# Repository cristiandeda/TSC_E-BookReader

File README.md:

# TSC_E-BookReader

## Diagrama bloc:

## Pasi de implementare:

- Am creat **schema electrica** pe baza celei atasate in cerinta, folosind biblioteca `DeskAssistant`
- Am creat apoi **PCB**-ul:
    - am modificat dimensiunile PCB-ului pentru a corespunde cu cele descrise in cerinta
    -  am plasat componentele in functie de schema electrica, grupandu-le pe baza 'functionalitatii'
    -  am decupat PCB-ul conform fisierului atasat in enunt
    -  am modificat denumirile *test-pad-urilor* - *TP* in functie de semnalele pe care le poarta
    -  am facut autorutare cu dimensiunile traseelor de alimentare precizate in enunt (`VBUS`, `VUSB`, `VBAT`, `3V3`, `EPD_3V3` si `EPD_3V3_C` cu *CopperWidth* de minimum **0.3 mm**, iar restul cu *CopperWidth* de minimum **0.15 mm**)
    -  am trasat planurile de masa (*top* si *bottom*)
- Am introdus modelele **3D**:
    - am descarcat modelele 3D corespunzatoare de pe [Component Search Engine](https://componentsearchengine.com/)
    - am editat fiecare componenta, adaugandu-i modelul 3D pe care l-am pozitionat conform *pinilor* / *footprint-ului*
- Am desenat modelele **3D** pentru *baterie*, *ecran* si *test-pad-uri* tinand cont de dimensiuni
- Am adaugat toate piesele (*placuta*, *ecranul*, *bateria* si *carcasa*) obtinand produsul final

## Descriere functionalitate hardware:

### 1. Alimentare și Protecție (USB-C & ESD)
- **Conector USB-C**: permite alimentarea plăcii și comunicarea de date.
- **PFMF.050.1**, **TVS diode (D1)**: oferă protecție la supratensiuni și descărcări electrostatice.
- **IC1**: convertește tensiunea de intrare (5V) la 3.3V, necesară pentru alimentarea circuitelor logice (ESP32, senzori, etc.).

### 2. Control Alimentare Baterie
- **MCP73831** este un controler de încărcare pentru baterii Li-Po.
- **C1, C2** filtrează zgomotele pe linia de alimentare.
- Permite alimentarea sistemului din baterie reîncărcabilă și oferă protecție la supraîncărcare/descărcare.

### 3. Nivel Încărcare Baterie
- **MAX17048** măsoară nivelul de încărcare al bateriei.
- Comunicarea se face prin magistrala I2C (SCL/SDA), comună cu alți senzori.
- Permite afișarea nivelului bateriei pe ecran sau transmiterea sa prin rețea.

### 4. Afișaj E-Paper
- **Header E-Paper** conectează un afișaj de tip E-Ink.
- **Driverul de semnal (MBR0530, L1, Q3)** controlează alimentarea și semnalele de comutare pentru afișaj.
- Selectarea tipului de ecran se face cu jumperul **S1**.
- Afișajul e-paper este ideal pentru consum redus de energie.

### 5. Modul RTC (Ceas în timp real)
- **DS3231SN** menține ora exactă, chiar și când placa este oprită.
- Funcționează pe I2C și are o baterie de rezervă.

### 6. Senzor Ambiental (BME688)
- Măsoară temperatură, umiditate, presiune și calitatea aerului.
- Se conectează la ESP32 prin I2C.

### 7. Memorie NOR Flash externă (64MB)
- **W25Q512JVEIQ** este o memorie SPI folosită pentru stocare extinsă (ex: cărți, imagini, date).
- Conectată la ESP32 pe interfață SPI (IO4–IO7).
- Permite stocarea persistentă a fișierelor.

### 8. Cititor Card SD
- Slot SD conectat prin SPI (IO8–IO11).
- Permite acces la fișiere externe, jurnalizare sau încărcare de date din card.

### 9. ESP32-C6 - Microcontroller Principal
- Conectează toate perifericele și controlează logica sistemului.
- Suportă Wi-Fi 6, BLE 5.2 și Zigbee/Thread.
- Are GPIO configurate pentru SPI, I2C, UART și control E-Paper.
- Este nucleul care rulează software-ul aplicației.

### 10. Protecții ESD pe SPI & Qwiic
- Diodă **TVS** și rezistențe pe liniile SPI/Qwiic pentru protecție la ESD.
- Asigură durabilitate mai mare în aplicații reale.

### 11. Butoane - Reset & Boot
- Buton **RESET**: Repornește ESP32.
- Buton **BOOT**: Permite intrarea în mod de boot pentru programare.
- Ambele conectate la pini critici (EN, IO0).

### 12. Interfață Qwiic / Stemma QT
- Conector I2C standard (JST-SH 4 pini).
- Permite adăugarea rapidă de senzori sau module adiționale compatibile.

### 13. Test Pads
- Paduri expuse pentru GPIO-uri esențiale.
- Permit depanarea, măsurători și extinderea funcționalității.

---

## Descrierea pinilor ESP32-C6:

| Pin ESP32-C6 | Nume Semnal     | Componentă Asociată                   | Scop / Funcție                                           |
|--------------|------------------|----------------------------------------|-----------------------------------------------------------|
| GND          | GND              | Toate componentele                     | Masă comună pentru alimentare și semnal.                  |
| EN           | Enable           | Buton Reset                            | Resetează microcontrollerul la apăsare.                   |
| IO0          | GPIO0            | Buton BOOT                             | Intrare în modul de boot la apăsare.                      |
| IO1          | GPIO1            | Test Pad TP11                          | Test/debug sau I/O general.                               |
| IO2          | GPIO2            | Test Pad TP12                          | Test/debug sau I/O general.                               |
| IO3          | GPIO3            | Test Pad TP13                          | Test/debug sau I/O general.                               |
| IO4          | GPIO4            | SPI Flash (CS)                         | Chip Select pentru memoria NOR Flash externă.             |
| IO5          | GPIO5            | SPI Flash (CLK)                        | Clock SPI pentru memoria NOR Flash externă.               |
| IO6          | GPIO6            | SPI Flash (MISO)                       | Data Out din NOR Flash spre ESP32.                        |
| IO7          | GPIO7            | SPI Flash (MOSI)                       | Data In către NOR Flash de la ESP32.                      |
| IO8          | GPIO8            | SD Card (CS)                           | Chip Select pentru card SD.                               |
| IO9          | GPIO9            | SD Card (CLK)                          | Clock SPI pentru card SD.                                 |
| IO10         | GPIO10           | SD Card (MISO)                         | Date de pe card SD către ESP32.                           |
| IO11         | GPIO11           | SD Card (MOSI)                         | Date de la ESP32 către card SD.                           |
| IO12         | GPIO12           | E-Paper Header                         | Semnal pentru ecran E-Paper (ex: BUSY, RST etc.).         |
| IO13         | GPIO13           | E-Paper Header                         | Semnal pentru ecran E-Paper.                              |
| IO14         | GPIO14           | E-Paper Header                         | Semnal pentru ecran E-Paper.                              |
| IO15         | GPIO15           | E-Paper Header                         | Semnal pentru ecran E-Paper.                              |
| IO16         | GPIO16           | SCL (RTC & BME688)                     | I2C Clock comun pentru RTC și senzor de mediu.            |
| IO17         | GPIO17           | SDA (RTC & BME688)                     | I2C Data comun pentru RTC și senzor de mediu.             |
| IO18         | GPIO18           | UART_RX (Qwiic/Debug)                  | Recepție serială (debug sau Qwiic/StemMA).                |
| IO19         | GPIO19           | UART_TX (Qwiic/Debug)                  | Transmisie serială (debug sau Qwiic/StemMA).              |

## Bill of Materials (BOM):

| Componenta |        Link      |               Datasheet                |
|------------|------------------|----------------------------------------|
| ESP32-C6-WROOM-1-N8 | [Link](https://ro.mouser.com/ProductDetail/Espressif-Systems/ESP32-C6-WROOM-1-N8?qs=8Wlm6%252BaMh8ST02Gmwp74cw%3D%3D) | [Datasheet](https://ro.mouser.com/datasheet/2/891/Espressif_ESP32_C6_WROOM_1__Datasheet_V0_1_PRELIMI-3239987.pdf) |
| 112A-TAAR-R03_ATTEND | [Link](https://www.digikey.ro/ro/products/detail/attend-technology/112A-TAAR-R03/17633923) | [Datasheet](https://www.attend.com.tw/data/download/file/112A-TAAR-R03_Spec.pdf) |
| ADAFRUIT_LEDCHIP-LED0603 | [Link](https://www.snapeda.com/parts/KP-1608SURCK/Kingbright/view-part/?ref=search&t=LED%200603) | [Datasheet](https://www.snapeda.com/parts/KP-1608SURCK/Kingbright/datasheet/) |
| ESP32_WROVER_EAGLE-LTSPICE_RR0402 | [Link](https://www.snapeda.com/parts/RC0402FR-07226RL/Yageo/view-part/) | [Datasheet](https://www.snapeda.com/parts/RC0402FR-07226RL/Yageo/datasheet/) |
| ESP32_WROVER_EAGLE-LTSPICE_CC0402 | [Link](https://componentsearchengine.com/part-view/CC0402MRX5R5BB106/YAGEO) | [Datasheet](https://componentsearchengine.com/Datasheets/2/CC0402MRX5R5BB106.pdf) |
| RCL_CPOL-EUCT3528 | [Link](https://ro.mouser.com/ProductDetail/Vishay-Sprague/TR3B106K025C1300?qs=jCGqFXxTmLdffnuDkXzk1g%3D%3D) | [Datasheet](https://www.vishay.com/docs/40080/tr3.pdf) |
| ESP32_WROVER_SPARKFUN-DISCRETESEMI_MOSFET_PCH-DMG2305UX-7 | [Link](https://ro.mouser.com/ProductDetail/Diodes-Incorporated/DMG2305UX-7?qs=L1DZKBg7t5F%2FNBHrjfxC%252Bg%3D%3D) | [Datasheet](https://www.diodes.com/assets/Datasheets/DMG2305UX.pdf) |
| 744043680IND_4828-WE-TPC_WRE | [Link](https://www.digikey.sg/en/products/detail/w%C3%BCrth-elektronik/744043680/1638515) | [Datasheet](https://www.we-online.com/components/products/datasheet/744043680.pdf) |
| BD5229G-TR | [Link](https://ro.mouser.com/ProductDetail/ROHM-Semiconductor/BD5229G-TR?qs=4kLU8WoGk0vvnhrrYwdszw%3D%3D) | [Datasheet](https://fscdn.rohm.com/en/products/databook/datasheet/ic/power/voltage_detector/bd52xxg-e.pdf) |
| ESP32_WROVER_BME680_BME680 | [Link](https://ro.mouser.com/ProductDetail/Bosch-Sensortec/BME680?qs=v271MhAjFHjo0yA%2FC4OnDQ%3D%3D) | [Datasheet](https://ro.mouser.com/datasheet/2/783/BST_BME680_DS001-1509608.pdf) |
| BUTTON_CUSYOMV1 | [Link](https://ro.mouser.com/ProductDetail/Panasonic/EVQ-P7M01P?qs=rJ%252BziJWpysz0sJAzuCybtw%3D%3D) | [Datasheet](https://industry.panasonic.com/global/en/downloads/?file_cd=402906&tab=catalog&series_cd=3457) |
| CPH3225A | [Link](https://ro.mouser.com/ProductDetail/Seiko-Semiconductors/CPH3225A?qs=3etwrb1wR%252BhUOph6lAO7eg%3D%3D) | [Datasheet](https://ro.mouser.com/datasheet/2/360/Seiko_Instruments_MicroBattery_E_20230330_2024Jan_-3561061.pdf) |
| DS3231SN# | [Link](https://ro.mouser.com/ProductDetail/Analog-Devices-Maxim-Integrated/DS3231SN?qs=1eQvB6Dk1vhUlr8%2FOrV0Fw%3D%3D) | [Datasheet](https://ro.mouser.com/datasheet/2/609/DS3231-3421123.pdf) |
| ESP32C6_VARISTORCN1812 | [Link](https://eu.mouser.com/ProductDetail/KEMET/VC1812L501R008?qs=jj7GbYRQuOa1j1%2F3gPpdvQ%3D%3D) | [Datasheet](https://eu.mouser.com/datasheet/2/447/KEM_V0002_VC-3316862.pdf) |
| ESP32_WROVER_AVX---SD0805S020S1R0_AVX_SD0805S020S1R0_0_0AVX_SD0805S020S1R0_0_0 | [Link](https://eu.mouser.com/ProductDetail/KYOCERA-AVX/SD0805S020S1R0?qs=jCA%252BPfw4LHbpkAoSnwrdjw%3D%3D&utm_id=6470900573&utm_source=google&utm_medium=cpc&utm_marketing_tactic=emeacorp&gad_source=1&gbraid=0AAAAADn_wf2CZaBvMXoqDoLB8a6wI1EC_&gclid=CjwKCAjw--K_BhB5EiwAuwYoyhyp4YPMQJxEs9O7Um1pbb_qrwD9UbwWFHYqYH_KvU5-nXs4CTfFVRoCY7kQAvD_BwE) | [Datasheet](https://eu.mouser.com/datasheet/2/40/schottky-3165252.pdf) |
| FH34SRJ-24S-0.5SH_99_ | [Link](https://eu.mouser.com/ProductDetail/Hirose-Connector/FH34SRJ-24S-05SH99?qs=vcbW%252B4%252BSTIpKBl5ap9J8Fw%3D%3D&utm_id=6470900573&utm_source=google&utm_medium=cpc&utm_marketing_tactic=emeacorp&gad_source=1&gbraid=0AAAAADn_wf2CZaBvMXoqDoLB8a6wI1EC_&gclid=CjwKCAjw--K_BhB5EiwAuwYoykKExbMK_Nf7-m2eYAFcWwWt_BaAKmDd5HmJ3DzOwus-MUIZVeL9ExoCTtAQAvD_BwE) | [Datasheet](https://eu.mouser.com/datasheet/2/185/FH34SRJ_24S_0_5SH_99__CL0580_1255_6_99_2DDrawing_0-1615044.pdf) |
| MAX17048G+T10 | [Link](https://eu.mouser.com/ProductDetail/Analog-Devices-Maxim-Integrated/MAX17048G+T10?qs=D7PJwyCwLAoGnnn8jEPRBQ%3D%3D&utm_id=20109199409&utm_source=google&utm_medium=cpc&utm_marketing_tactic=emeacorp&gad_source=1&gbraid=0AAAAADn_wf23I7VSL8Khkvz-kjEhjYqPz&gclid=CjwKCAjw--K_BhB5EiwAuwYoytVFz576awyE1ug3GUFRWVeGavv1g_gzDMEDxxjVwp1JIOS60JmKnhoC-zIQAvD_BwE) | [Datasheet](https://eu.mouser.com/datasheet/2/609/MAX17048_MAX17049-3469099.pdf) |
| MBR0530 | [Link](https://eu.mouser.com/ProductDetail/Micro-Commercial-Components-MCC/MBR0530-TP?qs=KFo7JewZbUECRHkxGanrdg%3D%3D&utm_id=6470900573&utm_source=google&utm_medium=cpc&utm_marketing_tactic=emeacorp&gad_source=1&gbraid=0AAAAADn_wf2CZaBvMXoqDoLB8a6wI1EC_&gclid=CjwKCAjw--K_BhB5EiwAuwYoysNC_AmHFOx6dFFFiTr86y8jRKC674aUhl0na6xIgHM9UWT_XyhG0RoCYwIQAvD_BwE) | [Datasheet](https://eu.mouser.com/datasheet/2/258/MBR0520_MBR0580_SOD123_-2492194.pdf) |
| ESP32_WROVER_SPARKFUN-IC-POWER_MCP73831 | [Link](https://ro.mouser.com/ProductDetail/Microchip-Technology/MCP73831-2DCI-MC?qs=hH%252BOa0VZEiBQ%2FrptDRXKdg%3D%3D) | [Datasheet](https://ro.mouser.com/datasheet/2/268/MCP73831_Family_Data_Sheet_DS20001984H-3441711.pdf) |
| PGB1010603MR | [Link](https://ro.mouser.com/ProductDetail/Littelfuse/PGB1010603MR?qs=gu7KAQ731URLg4GSnNNN7Q%3D%3D) | [Datasheet](https://www.littelfuse.com/assetdocs/pulseguard-esd-suppressors-pgb1-datasheet?assetguid=8a337998-d54d-466b-be4e-dc5bcd1f9321) |
| QWIIC_CONNECTORJS-1MM | [Link](https://www.sparkfun.com/qwiic-jst-connector-smd-4-pin-vertical.html) | [Datasheet](https://www.jst-mfg.com/product/pdf/eng/eSH.pdf?5ec58813d214e) |
| SAMACSYS_PARTS_USB4110-GF-A | [Link](https://eu.mouser.com/ProductDetail/GCT/USB4110-GF-A?qs=KUoIvG%2F9IlYiZvIXQjyJeA%3D%3D&utm_id=6470900573&utm_source=google&utm_medium=cpc&utm_marketing_tactic=emeacorp&gad_source=1&gbraid=0AAAAADn_wf2CZaBvMXoqDoLB8a6wI1EC_&gclid=CjwKCAjw--K_BhB5EiwAuwYoyqoFYku-1KEnaVMBZNhraqam0ThMUfxlrF7A4GQ8Pqj9d6zLqr7juBoCrOEQAvD_BwE) | [Datasheet](https://eu.mouser.com/datasheet/2/837/GCT_USB4110_Product_Drawing___20k_cycles-3455479.pdf) |
| SI1308EDL-T1-GE3 | [Link](https://eu.mouser.com/ProductDetail/Vishay-Semiconductors/SI1308EDL-T1-GE3?qs=bX1%252BNvsK%2FBramh9tgpOaEw%3D%3D&utm_id=20109199409&utm_source=google&utm_medium=cpc&utm_marketing_tactic=emeacorp&gad_source=1&gbraid=0AAAAADn_wf23I7VSL8Khkvz-kjEhjYqPz&gclid=CjwKCAjw--K_BhB5EiwAuwYoyllRgbebqlW1QDUb9SQpEls061aMn76tZxer07jsniKXNOsDESHnSBoCkL8QAvD_BwE) | [Datasheet](https://www.vishay.com/docs/63399/si1308edl.pdf) |
| USBLC6-2SC6Y | [Link](https://eu.mouser.com/ProductDetail/STMicroelectronics/USBLC6-2SC6Y?qs=gNDSiZmRJS%2FOgDexvXkdow%3D%3D&srsltid=AfmBOoqlX0fgvKlHMd5oyRC9Sr6hBsf51Zi0RKmaIGejNRz6zsEP_LgY) | [Datasheet](https://eu.mouser.com/datasheet/2/389/usblc6_2sc6y-1852505.pdf) |
| SJ | [Link](https://grabcad.com/library/solder-jumpers-1) | [Datasheet]() |
| W25Q512JVEIQ | [Link](https://eu.mouser.com/ProductDetail/Winbond/W25Q512JVEIQ?qs=l7cgNqFNU1jw6svr3at6tA%3D%3D&srsltid=AfmBOopwp-NQhQ6JM3w-WMYdzldr5QNIm_7CdLwVaaaS66y9swf4PMgu) | [Datasheet](https://eu.mouser.com/datasheet/2/949/Winbond_W25Q512JV_Datasheet-3240039.pdf) |
| XC6220A331MR-G | [Link](https://eu.mouser.com/ProductDetail/Torex-Semiconductor/XC6220A331MR-G?qs=AsjdqWjXhJ8ZSWznL1J0gg%3D%3D&srsltid=AfmBOopNlEzK7MdHRFabPSVSf32rb8GhsgKYTsuSlo8EjEXWvzOc5IIo) | [Datasheet](https://eu.mouser.com/datasheet/2/760/xc6220-3371556.pdf) |

## Probleme:

- Am aprobat 2 erori tip *SMD-Hole* la rutarea *PCB-ului*
- Am aprobat erorile de tip *part X has no value* sau *pin X connected to Y* ce apareau dupa rularea *ERC-ului* in schematic
- Pentru *Test-pad-uri* am creat eu un model 3D cilindric, deoarece nu am gasit model pe internet

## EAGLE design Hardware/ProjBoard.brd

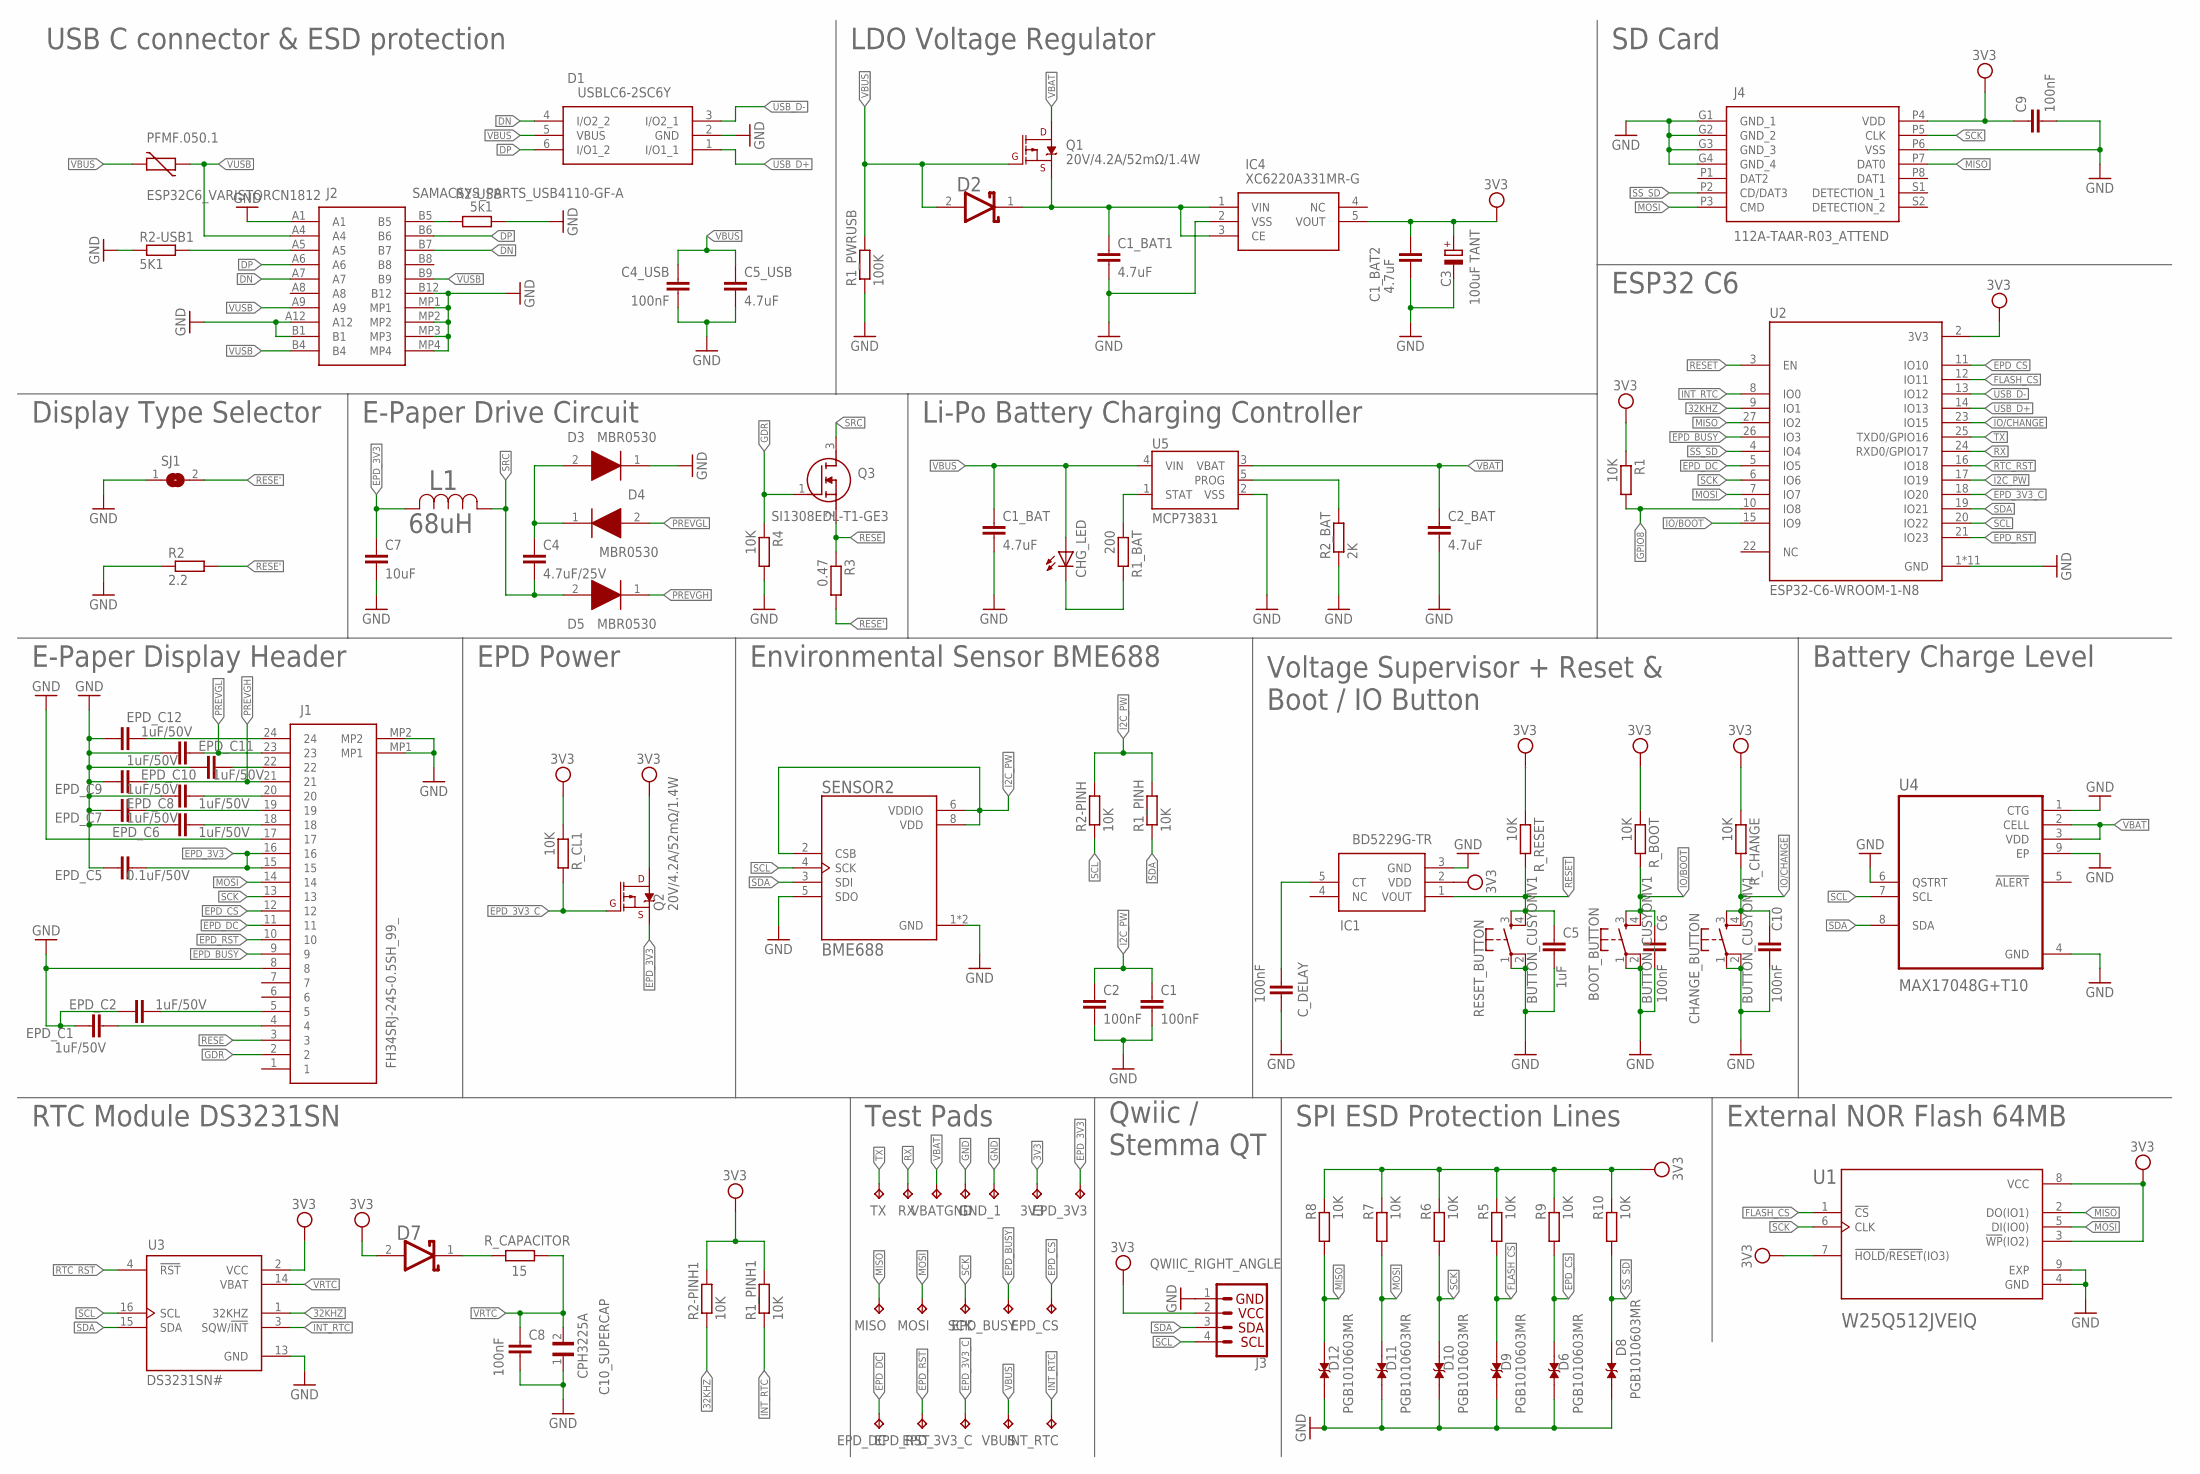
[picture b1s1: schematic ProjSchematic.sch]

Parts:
3V3: TPTP20R; TP20R
BOOT_BUTTON: BUTTON_CUSYOMV1; MYBUTTON
C1, C2, C4_USB, C6, C8, C9, C10: 100nF; ESP32_WROVER_EAGLE-LTSPICE_C0402
C1_BAT, C1_BAT1, C1_BAT2, C2_BAT, C5_USB: 4.7uF; ESP32_WROVER_EAGLE-LTSPICE_C0402
C3: 100uF TANT; RCL_CT3528
C4: 4.7uF/25V; ESP32_WROVER_EAGLE-LTSPICE_C0402
C5: 1uF; ESP32_WROVER_EAGLE-LTSPICE_C0402
C7: 10uF; ESP32_WROVER_EAGLE-LTSPICE_C0402
C10_SUPERCAP: CPH3225A; CAPCP3225X100N
CHANGE_BUTTON: BUTTON_CUSYOMV1; MYBUTTON
CHG_LED: ADAFRUIT_LEDCHIP-LED0603; ADAFRUIT_CHIP-LED0603
C_DELAY: 100nF; ESP32_WROVER_EAGLE-LTSPICE_C0402
D1: USBLC6-2SC6Y; SOT95P280X145-6N
D2, D7: ESP32_WROVER_AVX---SD0805S020S1R0_AVX_SD0805S020S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; ESP32_WROVER_AVX---SD0805S020S1R0_AVX_SD0805S020S1R0_0
D3, D4, D5: MBR0530; SOD3716X135N
D6, D8, D9, D10, D11, D12: PGB1010603MR; DIOC1608X36N
EPD_3V3, EPD_3V3_C: TPTP20R; TP20R
EPD_BUSY: TPTP20R; TP20R
EPD_C1, EPD_C2, EPD_C6, EPD_C7, EPD_C8, EPD_C9, EPD_C10, EPD_C11, EPD_C12: 1uF/50V; ESP32_WROVER_EAGLE-LTSPICE_C0402
EPD_C5: 0.1uF/50V; ESP32_WROVER_EAGLE-LTSPICE_C0402
EPD_CS: TPTP20R; TP20R
EPD_DC: TPTP20R; TP20R
EPD_RST: TPTP20R; TP20R
GND: TPTP20R; TP20R
GND_1: TPTP20R; TP20R
IC1: BD5229G-TR; SOT95P280X125-5N
IC4: XC6220A331MR-G; SOT95P280X120-5N
INT_RTC: TPTP20R; TP20R
J1: FH34SRJ-24S-0.5SH_99_; FH34SRJ24S05SH99
J2: SAMACSYS_PARTS_USB4110-GF-A; SAMACSYS_PARTS_USB4110GFA
J3: QWIIC_RIGHT_ANGLE; JST04_1MM_RA
J4: 112A-TAAR-R03_ATTEND; 112ATAARR03ATTEND
L1: 68uH; IND_4828-WE-TPC_WRE
MISO: TPTP20R; TP20R
MOSI: TPTP20R; TP20R
PFMF.050.1: ESP32C6_VARISTORCN1812; ESP32C6_VARISTOR_CT/CN1812
Q1, Q2: 20V/4.2A/52mΩ/1.4W; ESP32_WROVER_SPARKFUN-DISCRETESEMI_SOT23-3
Q3: SI1308EDL-T1-GE3; SOT65P210X110-3N
R1, R1_PINH, R1_PINH1, R2-PINH, R2-PINH1, R4, R5, R6, R7, R8, R9, R10: 10K; ESP32_WROVER_EAGLE-LTSPICE_R0402
R1_BAT: 200; ESP32_WROVER_EAGLE-LTSPICE_R0402
R1_PWRUSB: 100K; ESP32_WROVER_EAGLE-LTSPICE_R0402
R2: 2.2; ESP32_WROVER_EAGLE-LTSPICE_R0402
R2-USB: 5k1; ESP32_WROVER_EAGLE-LTSPICE_R0402
R2-USB1: 5K1; ESP32_WROVER_EAGLE-LTSPICE_R0402
R2_BAT: 2K; ESP32_WROVER_EAGLE-LTSPICE_R0402
R3: 0.47; ESP32_WROVER_EAGLE-LTSPICE_R0402
RESET_BUTTON: BUTTON_CUSYOMV1; MYBUTTON
RX: TPTP20R; TP20R
R_BOOT: 10K; ESP32_WROVER_EAGLE-LTSPICE_R0402
R_CAPACITOR: 15; ESP32_WROVER_EAGLE-LTSPICE_R0402
R_CHANGE: 10K; ESP32_WROVER_EAGLE-LTSPICE_R0402
R_CL1: 10K; ESP32_WROVER_EAGLE-LTSPICE_R0402
R_RESET: 10K; ESP32_WROVER_EAGLE-LTSPICE_R0402
SCK: TPTP20R; TP20R
SENSOR2: BME688; ESP32_WROVER_BME680_PSON80P300X300X100-8N
SJ1: SJ
TX: TPTP20R; TP20R
U1: W25Q512JVEIQ; SON127P600X800X80-9N
U2: ESP32-C6-WROOM-1-N8; XCVR_ESP32-C6-WROOM-1-N8
U3: DS3231SN#; SOIC127P1032X265-16N
U4: MAX17048G+T10; SON50P200X200X80-9N
U5: MCP73831; ESP32_WROVER_SPARKFUN-IC-POWER_SOT23-5
VBAT: TPTP20R; TP20R
VBUS: TPTP20R; TP20R

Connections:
3V3: 3V3.TP, C1_BAT2.1, C3.+, C9.1, D7.2 (ANODE), IC1.2 (VDD), IC4.5 (VOUT), J3.2, J4.P4 (VDD), Q2.3 (D), R1.1, R1_PINH1.2, R2-PINH1.2, R5.2, R6.2, R7.2, R8.2, R9.2, R10.2, R_BOOT.1, R_CHANGE.1, R_CL1.1, R_RESET.1, U1.3 (!WP!(IO2)), U1.7 (!HOLD!/!RESET!(IO3)), U1.8 (VCC), U2.2 (3V3), U3.2 (VCC)
32KHZ: R2-PINH1.1, U2.9 (IO1), U3.1 (32KHZ)
DN: D1.4 (I/O2_2), J2.A7, J2.B7
DP: D1.6 (I/O1_2), J2.A6, J2.B6
EPD_3V3: C7.1, EPD_3V3.TP, EPD_C5.2, J1.15, J1.16, L1.2, Q2.2 (S)
EPD_3V3_C: EPD_3V3_C.TP, Q2.1 (G), R_CL1.2, U2.18 (IO20)
EPD_BUSY: EPD_BUSY.TP, J1.9, U2.26 (IO3)
EPD_CS: D6.2, EPD_CS.TP, J1.12, R9.1, U2.11 (IO10)
EPD_DC: EPD_DC.TP, J1.11, U2.5 (IO5)
EPD_RST: EPD_RST.TP, J1.10, U2.21 (IO23)
FLASH_CS: D9.2, R5.1, U1.1 (!CS), U2.12 (IO11)
GDR: J1.2, Q3.1 (G), R4.1
GND: BOOT_BUTTON.1, BOOT_BUTTON.2, C1.2, C1_BAT.2, C1_BAT1.2, C1_BAT2.2, C2.2, C2_BAT.2, C3.-, C4_USB.2, C5.2, C5_USB.2, C6.2, C7.2, C8.2, C9.2, C10.2, C10_SUPERCAP.1, CHANGE_BUTTON.1, CHANGE_BUTTON.2, C_DELAY.2, D1.2 (GND), D3.1 (K), D6.1, D8.1, D9.1, D10.1, D11.1, D12.1, EPD_C1.2, EPD_C2.2, EPD_C5.1, EPD_C6.1, EPD_C7.1, EPD_C8.1, EPD_C9.1, EPD_C10.1, EPD_C11.1, EPD_C12.1, GND.TP, GND_1.TP, IC1.3 (GND), IC4.2 (VSS), J1.8, J1.17, J1.MP1, J1.MP2, J2.A1, J2.A12, J2.B1, J2.B12, J2.MP1, J2.MP2, J2.MP3, J2.MP4, J3.1, J4.G1 (GND_1), J4.G2 (GND_2), J4.G3 (GND_3), J4.G4 (GND_4), J4.P6 (VSS), R1_PWRUSB.1, R2.1, R2-USB.2, R2-USB1.1, R2_BAT.1, R4.2, RESET_BUTTON.1, RESET_BUTTON.2, SENSOR2.1 (GND), SENSOR2.5 (SDO), SENSOR2.7 (GND), SJ1.1, U1.4 (GND), U1.9 (EXP), U2.1 (GND), U2.28 (GND), U2.29_1 (GND), U2.29_2 (GND), U2.29_3 (GND), U2.29_4 (GND), U2.29_5 (GND), U2.29_6 (GND), U2.29_7 (GND), U2.29_8 (GND), U2.29_9 (GND), U3.13 (GND), U4.1 (CTG), U4.4 (GND), U4.6 (QSTRT), U4.9 (EP), U5.2 (VSS)
GPIO8: R1.2, U2.10 (IO8)
I2C_PW: C1.1, C2.1, R1_PINH.2, R2-PINH.2, SENSOR2.2 (CSB), SENSOR2.6 (VDDIO), SENSOR2.8 (VDD), U2.17 (IO19)
INT_RTC: INT_RTC.TP, R1_PINH1.1, U2.8 (IO0), U3.3 (SQW/!INT)
IO/BOOT: BOOT_BUTTON.3, BOOT_BUTTON.4, C6.1, R_BOOT.2, U2.15 (IO9)
IO/CHANGE: C10.1, CHANGE_BUTTON.3, CHANGE_BUTTON.4, R_CHANGE.2, U2.23 (IO15)
MISO: D12.2, J4.P7 (DAT0), MISO.TP, R8.1, U1.2 (DO(IO1)), U2.27 (IO2)
MOSI: D11.2, J1.14, J4.P3 (CMD), MOSI.TP, R7.1, U1.5 (DI(IO0)), U2.7 (IO7)
unnamed: J2.B5, R2-USB.1
unnamed: J2.A5, R2-USB1.2
unnamed: C1_BAT1.1, D2.1 (CATHODE), IC4.1 (VIN), IC4.3 (CE), Q1.2 (S)
unnamed: C4.1, D3.2 (A), D4.1 (K)
unnamed: CHG_LED.C, R1_BAT.2
unnamed: R1_BAT.1, U5.1 (STAT)
unnamed: EPD_C10.2, J1.22
unnamed: R2_BAT.2, U5.5 (PROG)
unnamed: C_DELAY.1, IC1.5 (CT)
unnamed: EPD_C1.1, J1.4
unnamed: EPD_C2.1, J1.5
unnamed: D7.1 (CATHODE), R_CAPACITOR.2
unnamed: EPD_C6.2, J1.18
unnamed: EPD_C7.2, J1.19
unnamed: EPD_C8.2, J1.20
unnamed: EPD_C12.2, J1.24
PREVGH: D5.1 (K), EPD_C9.2, J1.21
PREVGL: D4.2 (A), EPD_C11.2, J1.23
RESE: J1.3, Q3.2 (S), R3.1
RESE': R2.2, R3.2, SJ1.2
RESET: C5.1, IC1.1 (VOUT), RESET_BUTTON.3, RESET_BUTTON.4, R_RESET.2, U2.3 (EN)
RTC_RST: U2.16 (IO18), U3.4 (!RST)
RX: RX.TP, U2.24 (RXD0/GPIO17)
SCK: D10.2, J1.13, J4.P5 (CLK), R6.1, SCK.TP, U1.6 (CLK), U2.6 (IO6)
SCL: J3.4, R2-PINH.1, SENSOR2.4 (SCK), U2.20 (IO22), U3.16 (SCL), U4.7 (SCL)
SDA: J3.3, R1_PINH.1, SENSOR2.3 (SDI), U2.19 (IO21), U3.15 (SDA), U4.8 (SDA)
SRC: C4.2, D5.2 (A), L1.1, Q3.3 (D)
SS_SD: D8.2, J4.P2 (CD/DAT3), R10.1, U2.4 (IO4)
TX: TX.TP, U2.25 (TXD0/GPIO16)
USB_D+: D1.1 (I/O1_1), U2.14 (IO13)
USB_D-: D1.3 (I/O2_1), U2.13 (IO12)
VBAT: C2_BAT.1, Q1.3 (D), U4.2 (CELL), U4.3 (VDD), U5.3 (VBAT), VBAT.TP
VBUS: C1_BAT.1, C4_USB.1, C5_USB.1, CHG_LED.A, D1.5 (VBUS), D2.2 (ANODE), PFMF.050.1.2, Q1.1 (G), R1_PWRUSB.2, U5.4 (VIN), VBUS.TP
VRTC: C8.1, C10_SUPERCAP.2, R_CAPACITOR.1, U3.14 (VBAT)
VUSB: J2.A4, J2.A9, J2.B4, J2.B9, PFMF.050.1.1

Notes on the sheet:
USB C connector & ESD protection
LDO Voltage Regulator
SD Card
Display Type Selector
E-Paper Drive Circuit
Li-Po Battery Charging Controller
ESP32 C6
E-Paper Display Header
EPD Power
Environmental Sensor BME688
Voltage Supervisor + Reset & Boot / IO Button
Battery Charge Level
External NOR Flash 64MB
SPI ESD Protection Lines
Qwiic / Stemma QT
Test Pads
RTC Module DS3231SN

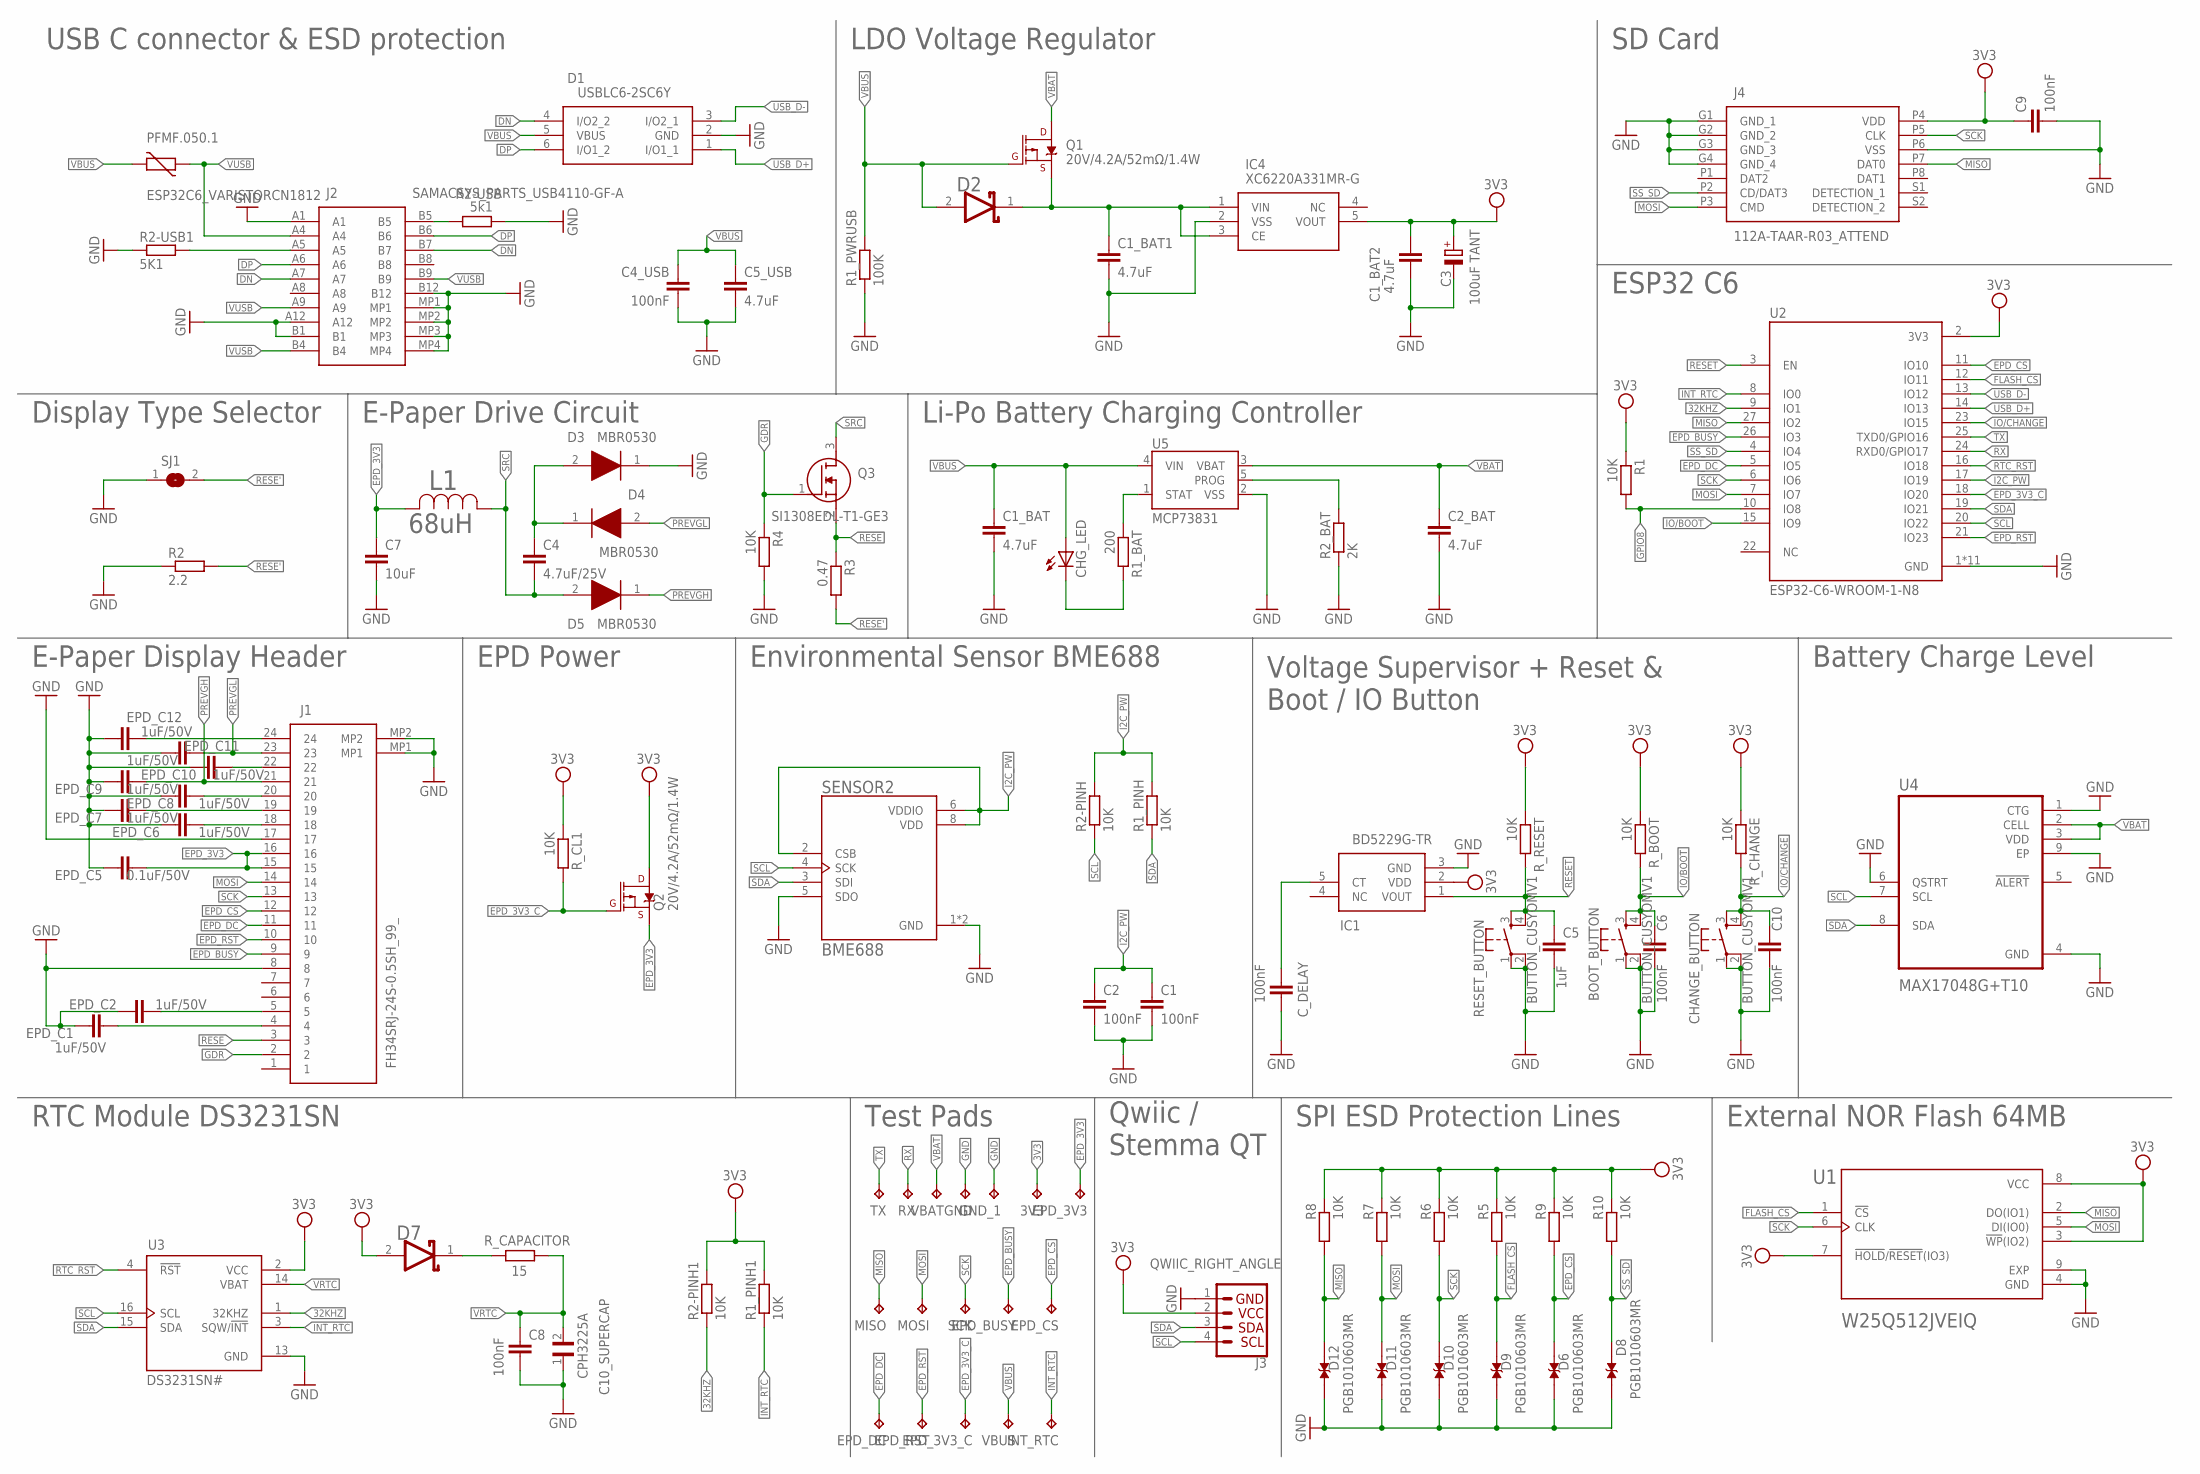
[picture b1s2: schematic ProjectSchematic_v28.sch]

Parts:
3V3: TPTP20R; TP20R
BOOT_BUTTON: BUTTON_CUSYOMV1; MYBUTTON
C1, C2, C4_USB, C6, C8, C9, C10: 100nF; ESP32_WROVER_EAGLE-LTSPICE_C0402
C1_BAT, C1_BAT1, C1_BAT2, C2_BAT, C5_USB: 4.7uF; ESP32_WROVER_EAGLE-LTSPICE_C0402
C3: 100uF TANT; RCL_CT3528
C4: 4.7uF/25V; ESP32_WROVER_EAGLE-LTSPICE_C0402
C5: 1uF; ESP32_WROVER_EAGLE-LTSPICE_C0402
C7: 10uF; ESP32_WROVER_EAGLE-LTSPICE_C0402
C10_SUPERCAP: CPH3225A; CAPCP3225X100N
CHANGE_BUTTON: BUTTON_CUSYOMV1; MYBUTTON
CHG_LED: ADAFRUIT_LEDCHIP-LED0603; ADAFRUIT_CHIP-LED0603
C_DELAY: 100nF; ESP32_WROVER_EAGLE-LTSPICE_C0402
D1: USBLC6-2SC6Y; SOT95P280X145-6N
D2, D7: ESP32_WROVER_AVX---SD0805S020S1R0_AVX_SD0805S020S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; ESP32_WROVER_AVX---SD0805S020S1R0_AVX_SD0805S020S1R0_0
D3, D4, D5: MBR0530; SOD3716X135N
D6, D8, D9, D10, D11, D12: PGB1010603MR; DIOC1608X36N
EPD_3V3, EPD_3V3_C: TPTP20R; TP20R
EPD_BUSY: TPTP20R; TP20R
EPD_C1, EPD_C2, EPD_C6, EPD_C7, EPD_C8, EPD_C9, EPD_C10, EPD_C11, EPD_C12: 1uF/50V; ESP32_WROVER_EAGLE-LTSPICE_C0402
EPD_C5: 0.1uF/50V; ESP32_WROVER_EAGLE-LTSPICE_C0402
EPD_CS: TPTP20R; TP20R
EPD_DC: TPTP20R; TP20R
EPD_RST: TPTP20R; TP20R
GND: TPTP20R; TP20R
GND_1: TPTP20R; TP20R
IC1: BD5229G-TR; SOT95P280X125-5N
IC4: XC6220A331MR-G; SOT95P280X120-5N
INT_RTC: TPTP20R; TP20R
J1: FH34SRJ-24S-0.5SH_99_; FH34SRJ24S05SH99
J2: SAMACSYS_PARTS_USB4110-GF-A; SAMACSYS_PARTS_USB4110GFA
J3: QWIIC_RIGHT_ANGLE; JST04_1MM_RA
J4: 112A-TAAR-R03_ATTEND; 112ATAARR03ATTEND
L1: 68uH; IND_4828-WE-TPC_WRE
MISO: TPTP20R; TP20R
MOSI: TPTP20R; TP20R
PFMF.050.1: ESP32C6_VARISTORCN1812; ESP32C6_VARISTOR_CT/CN1812
Q1, Q2: 20V/4.2A/52mΩ/1.4W; ESP32_WROVER_SPARKFUN-DISCRETESEMI_SOT23-3
Q3: SI1308EDL-T1-GE3; SOT65P210X110-3N
R1, R1_PINH, R1_PINH1, R2-PINH, R2-PINH1, R4, R5, R6, R7, R8, R9, R10: 10K; ESP32_WROVER_EAGLE-LTSPICE_R0402
R1_BAT: 200; ESP32_WROVER_EAGLE-LTSPICE_R0402
R1_PWRUSB: 100K; ESP32_WROVER_EAGLE-LTSPICE_R0402
R2: 2.2; ESP32_WROVER_EAGLE-LTSPICE_R0402
R2-USB: 5k1; ESP32_WROVER_EAGLE-LTSPICE_R0402
R2-USB1: 5K1; ESP32_WROVER_EAGLE-LTSPICE_R0402
R2_BAT: 2K; ESP32_WROVER_EAGLE-LTSPICE_R0402
R3: 0.47; ESP32_WROVER_EAGLE-LTSPICE_R0402
RESET_BUTTON: BUTTON_CUSYOMV1; MYBUTTON
RX: TPTP20R; TP20R
R_BOOT: 10K; ESP32_WROVER_EAGLE-LTSPICE_R0402
R_CAPACITOR: 15; ESP32_WROVER_EAGLE-LTSPICE_R0402
R_CHANGE: 10K; ESP32_WROVER_EAGLE-LTSPICE_R0402
R_CL1: 10K; ESP32_WROVER_EAGLE-LTSPICE_R0402
R_RESET: 10K; ESP32_WROVER_EAGLE-LTSPICE_R0402
SCK: TPTP20R; TP20R
SENSOR2: BME688; ESP32_WROVER_BME680_PSON80P300X300X100-8N
SJ1: SJ
TX: TPTP20R; TP20R
U1: W25Q512JVEIQ; SON127P600X800X80-9N
U2: ESP32-C6-WROOM-1-N8; XCVR_ESP32-C6-WROOM-1-N8
U3: DS3231SN#; SOIC127P1032X265-16N
U4: MAX17048G+T10; SON50P200X200X80-9N
U5: MCP73831; ESP32_WROVER_SPARKFUN-IC-POWER_SOT23-5
VBAT: TPTP20R; TP20R
VBUS: TPTP20R; TP20R

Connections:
3V3: 3V3.TP, C1_BAT2.1, C3.+, C9.1, D7.2 (ANODE), IC1.2 (VDD), IC4.5 (VOUT), J3.2, J4.P4 (VDD), Q2.3 (D), R1.1, R1_PINH1.2, R2-PINH1.2, R5.2, R6.2, R7.2, R8.2, R9.2, R10.2, R_BOOT.1, R_CHANGE.1, R_CL1.1, R_RESET.1, U1.3 (!WP!(IO2)), U1.7 (!HOLD!/!RESET!(IO3)), U1.8 (VCC), U2.2 (3V3), U3.2 (VCC)
32KHZ: R2-PINH1.1, U2.9 (IO1), U3.1 (32KHZ)
DN: D1.4 (I/O2_2), J2.A7, J2.B7
DP: D1.6 (I/O1_2), J2.A6, J2.B6
EPD_3V3: C7.1, EPD_3V3.TP, EPD_C5.2, J1.15, J1.16, L1.2, Q2.2 (S)
EPD_3V3_C: EPD_3V3_C.TP, Q2.1 (G), R_CL1.2, U2.18 (IO20)
EPD_BUSY: EPD_BUSY.TP, J1.9, U2.26 (IO3)
EPD_CS: D6.2, EPD_CS.TP, J1.12, R9.1, U2.11 (IO10)
EPD_DC: EPD_DC.TP, J1.11, U2.5 (IO5)
EPD_RST: EPD_RST.TP, J1.10, U2.21 (IO23)
FLASH_CS: D9.2, R5.1, U1.1 (!CS), U2.12 (IO11)
GDR: J1.2, Q3.1 (G), R4.1
GND: BOOT_BUTTON.1, BOOT_BUTTON.2, C1.2, C1_BAT.2, C1_BAT1.2, C1_BAT2.2, C2.2, C2_BAT.2, C3.-, C4_USB.2, C5.2, C5_USB.2, C6.2, C7.2, C8.2, C9.2, C10.2, C10_SUPERCAP.1, CHANGE_BUTTON.1, CHANGE_BUTTON.2, C_DELAY.2, D1.2 (GND), D3.1 (K), D6.1, D8.1, D9.1, D10.1, D11.1, D12.1, EPD_C1.2, EPD_C2.2, EPD_C5.1, EPD_C6.1, EPD_C7.1, EPD_C8.1, EPD_C9.1, EPD_C10.1, EPD_C11.1, EPD_C12.1, GND.TP, GND_1.TP, IC1.3 (GND), IC4.2 (VSS), J1.8, J1.17, J1.MP1, J1.MP2, J2.A1, J2.A12, J2.B1, J2.B12, J2.MP1, J2.MP2, J2.MP3, J2.MP4, J3.1, J4.G1 (GND_1), J4.G2 (GND_2), J4.G3 (GND_3), J4.G4 (GND_4), J4.P6 (VSS), R1_PWRUSB.1, R2.1, R2-USB.2, R2-USB1.1, R2_BAT.1, R4.2, RESET_BUTTON.1, RESET_BUTTON.2, SENSOR2.1 (GND), SENSOR2.5 (SDO), SENSOR2.7 (GND), SJ1.1, U1.4 (GND), U1.9 (EXP), U2.1 (GND), U2.28 (GND), U2.29_1 (GND), U2.29_2 (GND), U2.29_3 (GND), U2.29_4 (GND), U2.29_5 (GND), U2.29_6 (GND), U2.29_7 (GND), U2.29_8 (GND), U2.29_9 (GND), U3.13 (GND), U4.1 (CTG), U4.4 (GND), U4.6 (QSTRT), U4.9 (EP), U5.2 (VSS)
GPIO8: R1.2, U2.10 (IO8)
I2C_PW: C1.1, C2.1, R1_PINH.2, R2-PINH.2, SENSOR2.2 (CSB), SENSOR2.6 (VDDIO), SENSOR2.8 (VDD), U2.17 (IO19)
INT_RTC: INT_RTC.TP, R1_PINH1.1, U2.8 (IO0), U3.3 (SQW/!INT)
IO/BOOT: BOOT_BUTTON.3, BOOT_BUTTON.4, C6.1, R_BOOT.2, U2.15 (IO9)
IO/CHANGE: C10.1, CHANGE_BUTTON.3, CHANGE_BUTTON.4, R_CHANGE.2, U2.23 (IO15)
MISO: D12.2, J4.P7 (DAT0), MISO.TP, R8.1, U1.2 (DO(IO1)), U2.27 (IO2)
MOSI: D11.2, J1.14, J4.P3 (CMD), MOSI.TP, R7.1, U1.5 (DI(IO0)), U2.7 (IO7)
unnamed: J2.B5, R2-USB.1
unnamed: J2.A5, R2-USB1.2
unnamed: C1_BAT1.1, D2.1 (CATHODE), IC4.1 (VIN), IC4.3 (CE), Q1.2 (S)
unnamed: C4.1, D3.2 (A), D4.1 (K)
unnamed: CHG_LED.C, R1_BAT.2
unnamed: R1_BAT.1, U5.1 (STAT)
unnamed: EPD_C10.2, J1.22
unnamed: R2_BAT.2, U5.5 (PROG)
unnamed: C_DELAY.1, IC1.5 (CT)
unnamed: EPD_C1.1, J1.4
unnamed: EPD_C2.1, J1.5
unnamed: D7.1 (CATHODE), R_CAPACITOR.2
unnamed: EPD_C6.2, J1.18
unnamed: EPD_C7.2, J1.19
unnamed: EPD_C8.2, J1.20
unnamed: EPD_C12.2, J1.24
PREVGH: D5.1 (K), EPD_C9.2, J1.21
PREVGL: D4.2 (A), EPD_C11.2, J1.23
RESE: J1.3, Q3.2 (S), R3.1
RESE': R2.2, R3.2, SJ1.2
RESET: C5.1, IC1.1 (VOUT), RESET_BUTTON.3, RESET_BUTTON.4, R_RESET.2, U2.3 (EN)
RTC_RST: U2.16 (IO18), U3.4 (!RST)
RX: RX.TP, U2.24 (RXD0/GPIO17)
SCK: D10.2, J1.13, J4.P5 (CLK), R6.1, SCK.TP, U1.6 (CLK), U2.6 (IO6)
SCL: J3.4, R2-PINH.1, SENSOR2.4 (SCK), U2.20 (IO22), U3.16 (SCL), U4.7 (SCL)
SDA: J3.3, R1_PINH.1, SENSOR2.3 (SDI), U2.19 (IO21), U3.15 (SDA), U4.8 (SDA)
SRC: C4.2, D5.2 (A), L1.1, Q3.3 (D)
SS_SD: D8.2, J4.P2 (CD/DAT3), R10.1, U2.4 (IO4)
TX: TX.TP, U2.25 (TXD0/GPIO16)
USB_D+: D1.1 (I/O1_1), U2.14 (IO13)
USB_D-: D1.3 (I/O2_1), U2.13 (IO12)
VBAT: C2_BAT.1, Q1.3 (D), U4.2 (CELL), U4.3 (VDD), U5.3 (VBAT), VBAT.TP
VBUS: C1_BAT.1, C4_USB.1, C5_USB.1, CHG_LED.A, D1.5 (VBUS), D2.2 (ANODE), PFMF.050.1.2, Q1.1 (G), R1_PWRUSB.2, U5.4 (VIN), VBUS.TP
VRTC: C8.1, C10_SUPERCAP.2, R_CAPACITOR.1, U3.14 (VBAT)
VUSB: J2.A4, J2.A9, J2.B4, J2.B9, PFMF.050.1.1

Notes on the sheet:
USB C connector & ESD protection
LDO Voltage Regulator
SD Card
Display Type Selector
E-Paper Drive Circuit
Li-Po Battery Charging Controller
ESP32 C6
E-Paper Display Header
EPD Power
Environmental Sensor BME688
Voltage Supervisor + Reset & Boot / IO Button
Battery Charge Level
External NOR Flash 64MB
SPI ESD Protection Lines
Qwiic / Stemma QT
Test Pads
RTC Module DS3231SN

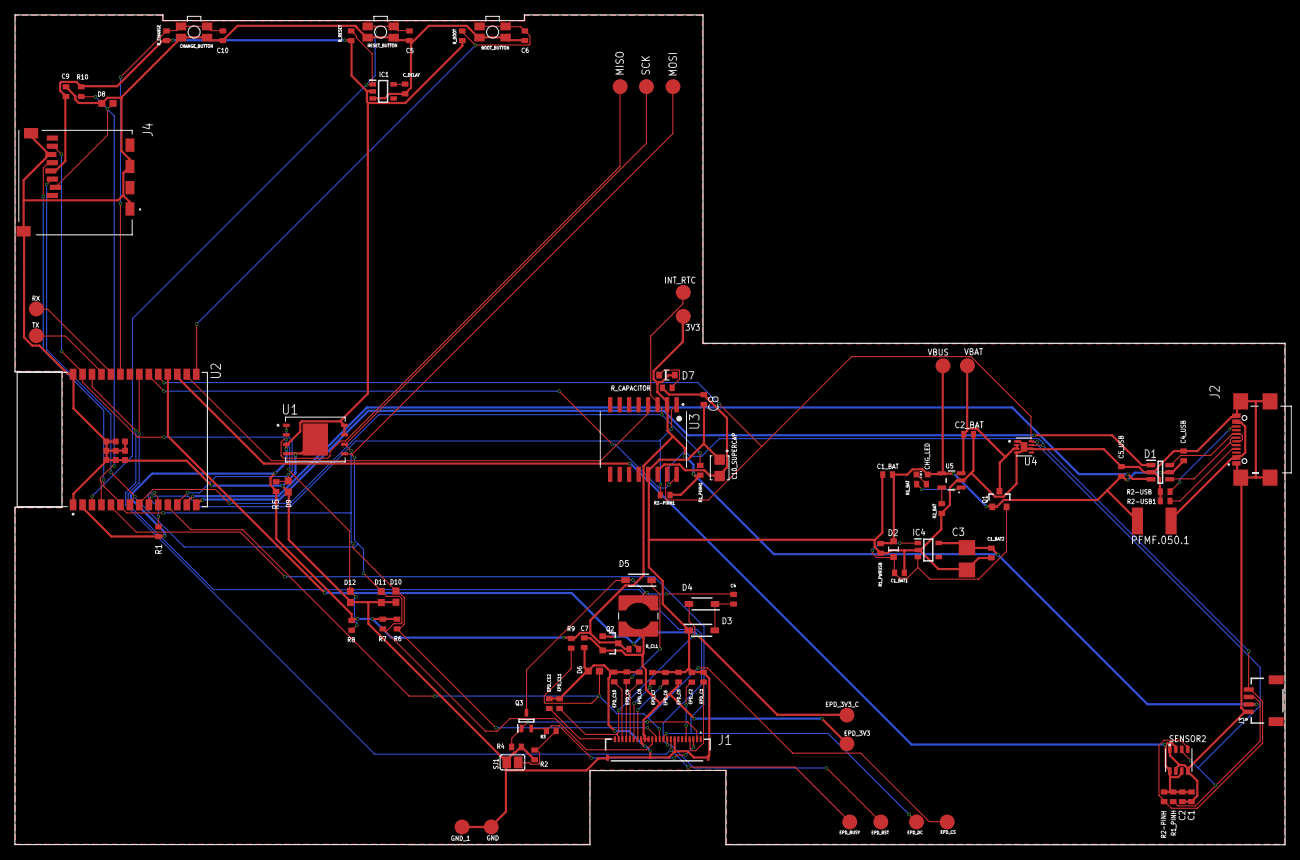
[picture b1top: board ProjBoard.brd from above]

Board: 2 copper layers, 170.2 x 111.2 mm, 103 parts (0 on the bottom side), 55 nets.

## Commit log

2025-04-04 Created LICENSE
2025-04-06 Added project files
2025-04-06 Added diagram
2025-04-06 Added diagram to README
2025-04-10 [Update schematic] - solved some errors
2025-04-10 [Update board] - solved some errors
2025-04-10 Uploaded new images
2025-04-10 [Update] - new diagram
2025-04-10 Added new diagram to README
2025-04-10 Added updated 3D model files
2025-04-10 Added updated BOM file
2025-04-11 Updated README - partial BOM
2025-04-11 Added README - final
2025-04-11 Added README - final v2

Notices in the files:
parts and their libraries:
COPYRIGHT: Copyright (C) 2024 Ultra Librarian. All rights reserved.
